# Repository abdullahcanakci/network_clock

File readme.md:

[TOC]

### What is this?

This is the second version of my clock with network time keeping with ESP12-E/F variant. On chip time keeping is good but as I experienced with DS3231 it drifts about a minute every two days. Which is not good for long time time keeping without interaction.

---

Finally I have received the board. It worked great apart from micro usb port, which was pain to solder.

---

#### Design Limits

For this project I want to have a real PCB so I won't have to fiddle with protoboards and point-to-point soldering. Also replicating a device would be so easy with a PCB.

For PCB manufacturing I shopped around my local fabs, they wanted an arm and a leg. They have a lead time of 1 month and DHL shipping which I thought they really outsource their production.

For a cheaper alternative there is JLCPCB which is cheap for board smaller than 100mm on the long side. For I couldn't really found a comparable source I have to accept their restrictions.

For display I will use 7-Segment displays with separate digits. Just because most of them are sharing their pin out I can just change them with a equivalent one easily if need arises. Biggest displays I can fit into 100 mm board is 1" character height ones which has 24-25 mm width.

---

#### Road map

Creating this device will be 4 part endeavor.

1. Hardware Selection
2. Implementation
3. Prototyping
4. Finishing

##### Hardware Selection

Can be found on Parts list.

##### Implementation

Implementation is mostly about wiring diagram and code. Both of these are done on breadboard and in minimum working order as of Jun 7, 2019. 

##### Prototyping

A prototype PCB has been sent for production in Jun 5, 2019, after receiving I will add required peripherals for interaction, better layout etc. and update the project.

By July 1, I received the boards and checked if everything was in working order. More can be found on [Prototype].

##### Finishing

Hopefully by this time everything works as expected and I wrap the project.

---

#### Parts list

|      | Name               | Description                          | Quantity |
| ---- | ------------------ | ------------------------------------ | -------- |
| 1    | ESP-12 E/F variant | uC with networking capabilities.     | 1        |
| 2    | MAX7219CWG         | Display driver with serial interface | 1        |
| 3    | AMS1117-3.3        | 3V3 voltage regulator                | 1        |
| 4    | E6-1100CUR1        | 7 Segment Display. 1" Digit height   | 4        |
| 5    | DTS-3 / STS-3      | Tactile Swich                        | 4        |
| 6    | Leds 0805(2012)    | Status leds.                         | 2        |
| 7    | 220 Ohm            | Current limit resistor for leds      | 2        |
| 8    | 10K Ohm            | Pull-up/down resistor                | 4        |
| 9    | 47K Ohm            | Max7219 current reference resistor   | 1        |
| 10   | 100nF 0805(2012)   | Decoupling capacitor                 | 2        |
| 11   | 10uF 2.5mm pitch   | Bulk capacitor for displays.         | 1        |
| 12   | 0.1"x6 header      | Serial programming header            | 1        |
| 13   |                    | Micro USB type b connector           |          |

1. ESP-12E/F for microcontroller. They are mostly same and can be interchangable.

2. MAX7219 is a serially interfaced led matrix driver. One plus of this chip is digital intensity configuration.

3. AMS1117-3.3 is a Linear voltage regulator we will use it to power our microcontroller. Display driver will use 5V direclty.

4. These displays are produced by "Strong Base Investment LTD". Datasheet can be found [here](https://img.ozdisan.com/ETicaret_Dosya/41608_1428544.pdf).  Any comparable display can be used. I left 3mm space around each display so a bit wider ones can also fit (Displays are 24mm wide, I put them inside 27mm.). As long as their pin position fits.

5. DTS-3 /STS-3 vs comparable switches can be used. Datasheet of a sample can be found [here](https://eu.mouser.com/ProductDetail/Diptronics/DTS-32N-V-B?qs=sGAEpiMZZMtFyPk3yBMYYD0iDqFNlT1wSP2u7Qqc2AE%3D).

11. 10uF bulk capacitor. Display driver is a bit power hungry. Can be substituted for no smaller than ~3uF capacitor. Board has place for 2.5mm pitch 5mm axial electrolytic capacitor. But also has place for it to lie down.
12. Regular 0.1" pitch header, pogo stick etc. can be used for programming. 
13. There are lots of Micro  USB type B connectors. I think it would be best to have a through hole one to have a better leverage against wear and tear. A comparable one can be found [here](https://eu.mouser.com/ProductDetail/Hirose-Connector/ZX62D-B-5PA830?qs=sGAEpiMZZMulM8LPOQ%252Byk6r3VmhUEyMLT8hu1C1GYL85FtczwhvFwQ%3D%3D). 

---

#### Prototype

Prototype board has been received and in working order. Final hardware design finished. Some updates  and changes from prototype board applied.

Changes made:

- Larger ground planes on both sides and more stiching.
- Thermal reliefs on all pads whether through hole or smt pad. It was hard to solder some pads on the prototype.
- Removed one of the commons connection from displays to ease routing.
- Larger board size. 42mm to 60mm. With mounting holes
- Prototype programming power source was 3V3 which wasn't enough for display driver. Changed to 5V.
- Better routing of signal traces.
- Wider trace width. 10 to 14 mil for regular, 15 to ~20mil for power traces.
- Removed Logic translator. No really need.
- Added status Leds.
- Added 4 buttons. WPS, REFRESH, OFFSET, RESET.

Schematic and the PCB gerber file can be found on the root.

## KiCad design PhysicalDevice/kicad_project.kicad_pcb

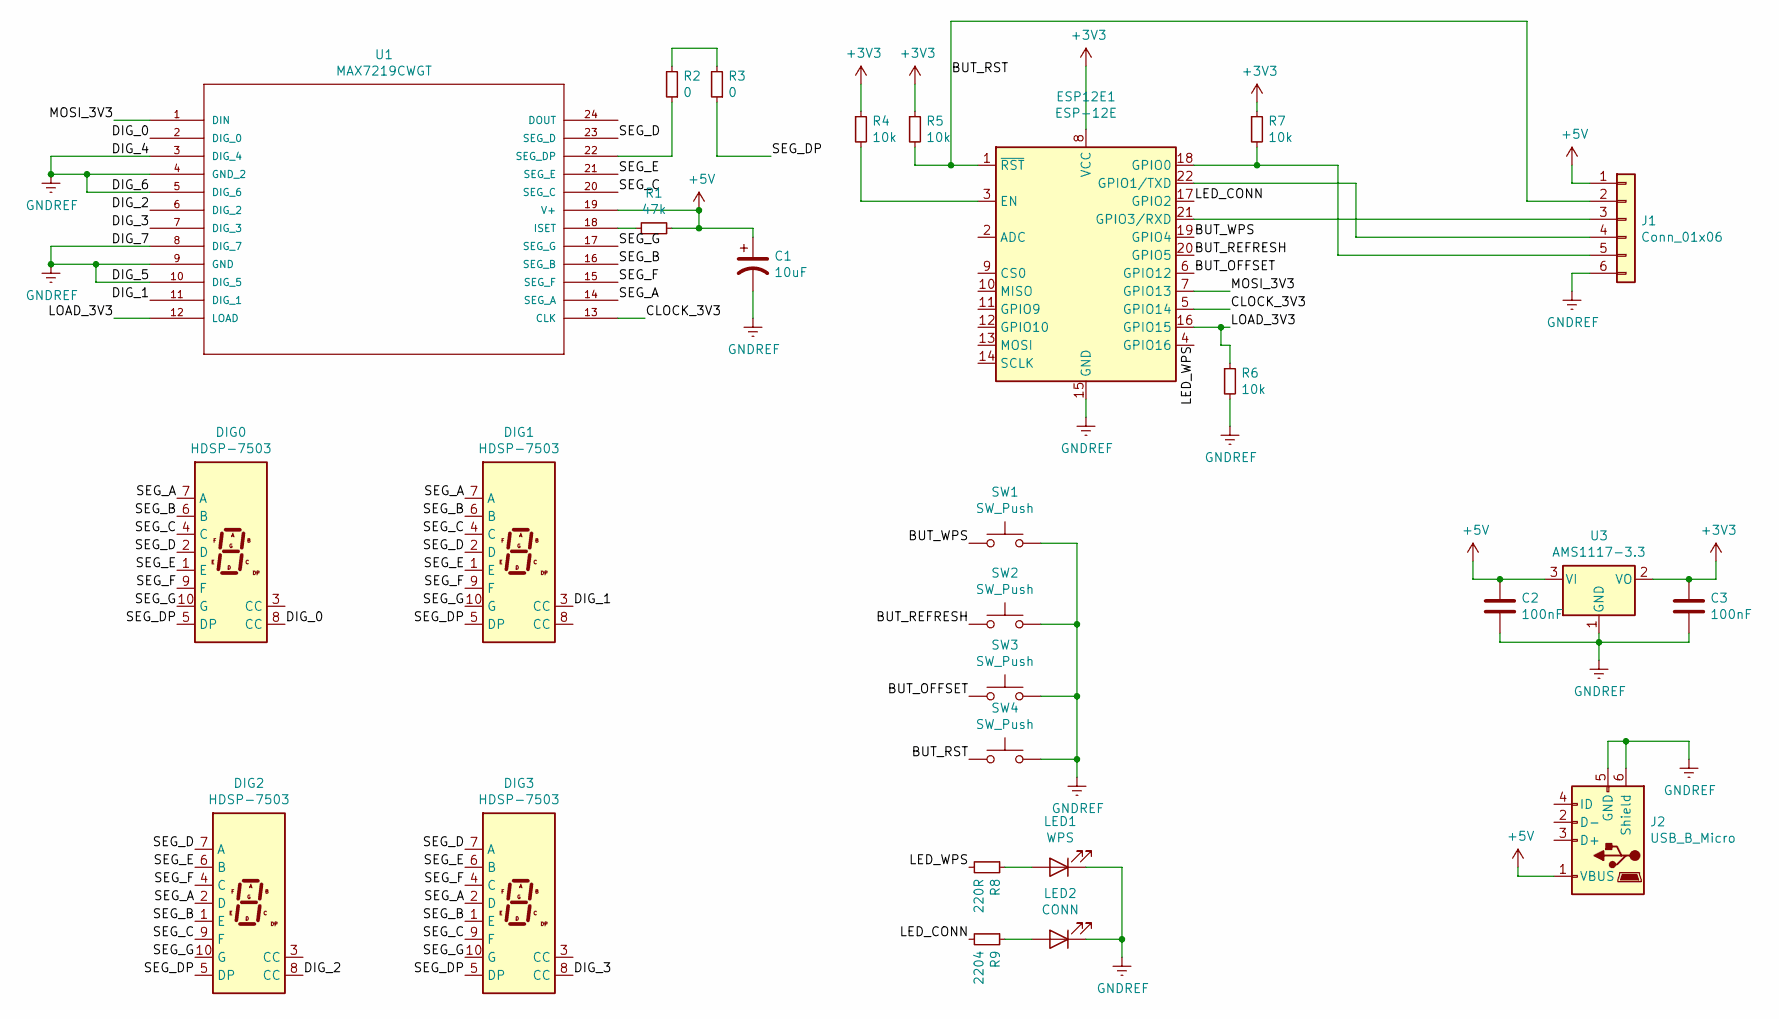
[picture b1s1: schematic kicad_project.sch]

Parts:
C1: 10uF; CP_Radial_D5.0mm_P2.50mm
C2, C3: 100nF; C_0805_2012Metric
DIG0, DIG1, DIG2, DIG3: HDSP-7503; E6-1100CUR1
ESP12E1: ESP-12E
J1: Conn_01x06; ProgrammingHeader
J2: USB_B_Micro; USB_Micro-B_Molex-105017-0001
LED1: WPS; LED_0805_2012Metric_Pad1.15x1.40mm_HandSolder
LED2: CONN; LED_0805_2012Metric_Pad1.15x1.40mm_HandSolder
R1: 47k; R_0805_2012Metric_Pad1.15x1.40mm_HandSolder
R2, R3: 0; R_0805_2012Metric_Pad1.15x1.40mm_HandSolder
R4, R5, R6, R7: 10k; R_0805_2012Metric_Pad1.15x1.40mm_HandSolder
R8: 220R; R_0805_2012Metric_Pad1.15x1.40mm_HandSolder
R9: 2204; R_0805_2012Metric_Pad1.15x1.40mm_HandSolder
SW1, SW2, SW3, SW4: SW_Push; DTS-3
U1: MAX7219CWGT; 21-0042B_24
U3: AMS1117-3.3; SOT-223-3_TabPin2

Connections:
+3V3: C3.1, ESP12E1.8 (VCC), R4.1, R5.1, R7.1, U3.2 (VO)
+5V: C1.1, C2.1, J1.1, J2.1 (VBUS), R1.2, U1.19 (V+), U3.3 (VI)
/BUT_OFFSET: ESP12E1.6 (GPIO12), SW3.1
/BUT_REFRESH: ESP12E1.20 (GPIO5), SW2.1
/BUT_RST: ESP12E1.1 (~RST), J1.2, R5.2, SW4.1
/BUT_WPS: ESP12E1.19 (GPIO4), SW1.1
/CLOCK_3V3: ESP12E1.5 (GPIO14), U1.13 (CLK)
/DIG_0: DIG0.8 (CC), U1.2 (DIG_0)
/DIG_1: DIG1.3 (CC), U1.11 (DIG_1)
/DIG_2: DIG2.8 (CC), U1.6 (DIG_2)
/DIG_3: DIG3.8 (CC), U1.7 (DIG_3)
/LED_CONN: ESP12E1.17 (GPIO2), R9.2
/LED_WPS: ESP12E1.4 (GPIO16), R8.2
/LOAD_3V3: ESP12E1.16 (GPIO15), R6.1, U1.12 (LOAD)
/MOSI_3V3: ESP12E1.7 (GPIO13), U1.1 (DIN)
/SEG_A: DIG0.7 (A), DIG1.7 (A), DIG2.2 (D), DIG3.2 (D), U1.14 (SEG_A)
/SEG_B: DIG0.6 (B), DIG1.6 (B), DIG2.1 (E), DIG3.1 (E), U1.16 (SEG_B)
/SEG_C: DIG0.4 (C), DIG1.4 (C), DIG2.9 (F), DIG3.9 (F), U1.20 (SEG_C)
/SEG_D: DIG0.2 (D), DIG1.2 (D), DIG2.7 (A), DIG3.7 (A), U1.23 (SEG_D)
/SEG_DP: DIG0.5 (DP), DIG1.5 (DP), DIG2.5 (DP), DIG3.5 (DP), R3.1
/SEG_E: DIG0.1 (E), DIG1.1 (E), DIG2.6 (B), DIG3.6 (B), U1.21 (SEG_E)
/SEG_F: DIG0.9 (F), DIG1.9 (F), DIG2.4 (C), DIG3.4 (C), U1.15 (SEG_F)
/SEG_G: DIG0.10 (G), DIG1.10 (G), DIG2.10 (G), DIG3.10 (G), U1.17 (SEG_G)
GNDREF: C1.2, C2.2, C3.2, ESP12E1.15 (GND), J1.6, J2.5 (GND), J2.6 (Shield), LED1.1 (K), LED2.1 (K), R6.2, SW1.2, SW2.2, SW3.2, SW4.2, U1.3 (DIG_4), U1.4 (GND_2), U1.5 (DIG_6), U1.8 (DIG_7), U1.9 (GND), U1.10 (DIG_5), U3.1 (GND)
unnamed: ESP12E1.3 (EN), R4.2
unnamed: ESP12E1.18 (GPIO0), J1.5, R7.2
unnamed: ESP12E1.21 (GPIO3/RXD), J1.3
unnamed: ESP12E1.22 (GPIO1/TXD), J1.4
unnamed: LED1.2 (A), R8.1
unnamed: LED2.2 (A), R9.1
unnamed: R1.1, U1.18 (ISET)
unnamed: R2.1, U1.22 (SEG_DP)
unnamed: R2.2, R3.2

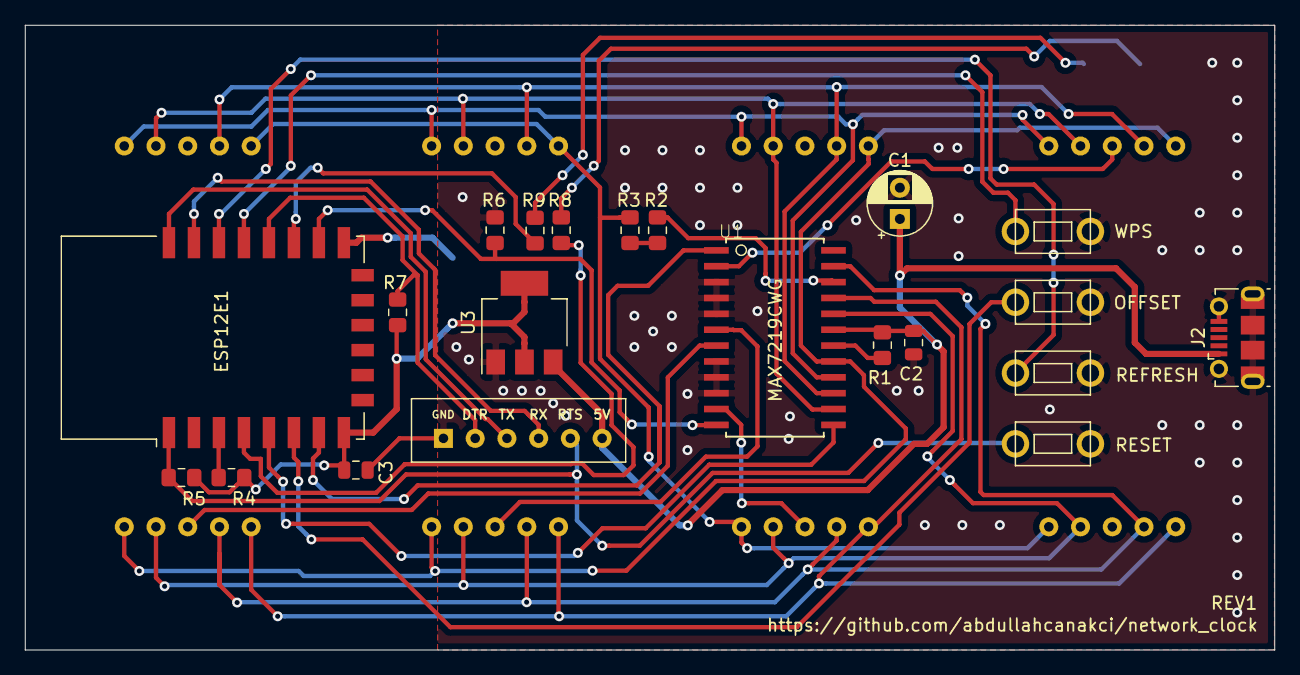
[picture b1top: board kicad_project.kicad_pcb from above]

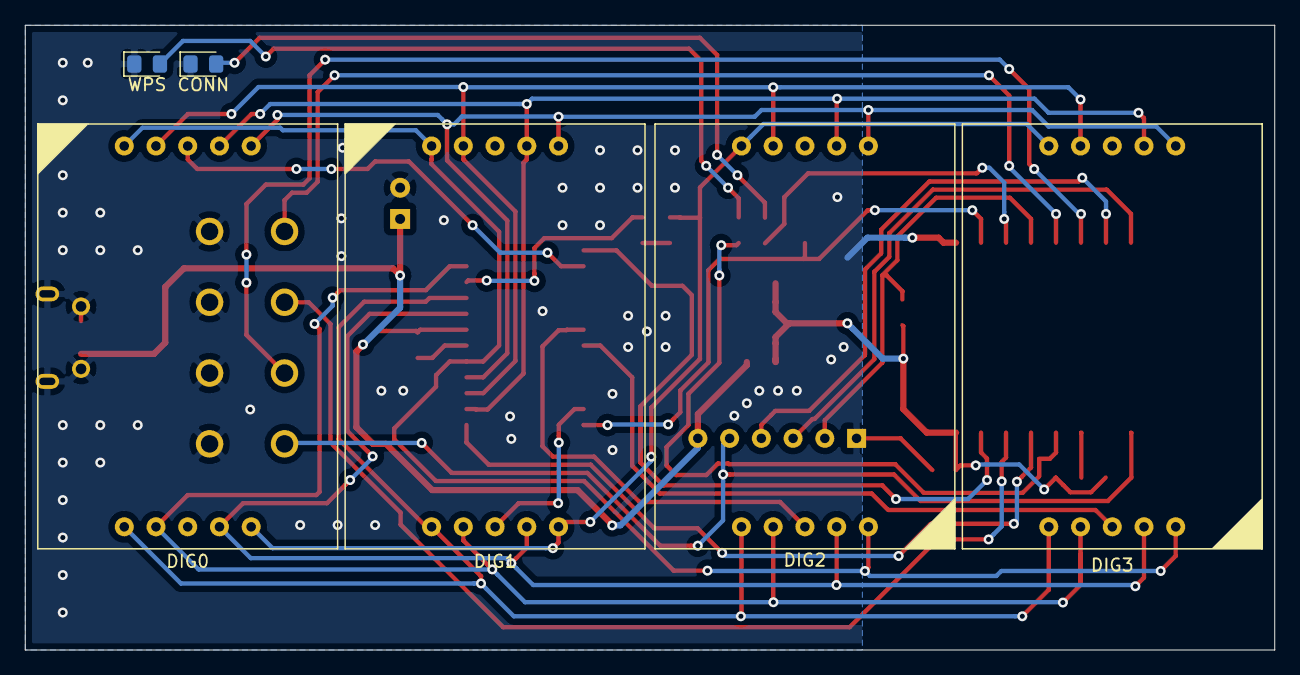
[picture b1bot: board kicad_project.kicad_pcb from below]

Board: 2 copper layers, 100.0 x 50.0 mm, 27 parts (6 on the bottom side), 33 nets.

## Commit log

2019-05-25 init
2019-05-26 Basic Serial Working. Specialization started.
    Basic serial is working. Created controllers for them and started working on them. This commit is before I gut the main.cpp
2019-05-26 Specialized controller for display
    Display is now controller by it's own class. Scanning works on first glance didn't check POV. Digit selecting works.
2019-05-26 Nodemcu problems fixed
    Nodemcu created problems when I want to use pins to drive mosfet gates. I fixed it with second 595 to create extra 8 bits of control to control mosfets. Persistence of vision works.
2019-05-26 fix delay
2019-05-27 Interrupt based updates. Time servers and parsing local timekeeping.
    Updates that need to be time sensitive moved to the Ticker from esp8266/arduinocore it works as expected.
    Display, UDP package checking clock dot etc are implemented.
    NTP time server connection implemented. for local timekeeping and parsing RTCLib from Adafruit used. I have used it before, familiar with it. May change with something smaller later.
    Time to display parsing imlemented, works.
2019-05-27 Dot is working.
2019-06-04 Move to MAX7219
    Okay, at first I was gonna use 595 as drivers and use 1" 7 segment led displays. The problem is there is not much displays with 1 chip per segment. With 595 I was gonna use sole 3V3 logic everywhere.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
2019-06-04 Code cleanup
2019-06-04 Fixed dot working.
    Relocated some code
2019-06-05 Updated readme. Schematic and PCB added
2019-06-07 updated and rewrote readme.md
2019-06-15 RTClib name mismatch fixed. Interrupts are moved into flag based events within loop()
2019-06-21 implemented rudimentary interrupt debouncing
2019-06-21 HW interrupt based Debounce removed.
2019-06-21 implemented refresh button and respective action
2019-06-24 WPS is implemented. EEPROM implemented.
2019-06-24 init physical device
2019-06-25 created schematic and routed pcb
2019-06-25 Board fully routed. Gerber file generated.
2019-06-26 added an extra button, 2 leds.
2019-06-26 added leds and rerouted some bits to be more tidy
2019-07-01 pre track witdh change
2019-07-01 changed min routing size from 0.25mm(~9.8mil) to 0.35(~13.4mil)
2019-07-02 removed kicad files. To much Clutter. Will update Gerber accordinly
2019-07-02 Added Gerber
2019-07-02 Removed Kicad Folder
2019-07-04 Added schematic and updated readme
2019-07-07 Basic server created. Basic webpage created. no interaction.
2019-07-08 Json answering works. Webpage mostly works
2019-07-08 Full exchange between server and client established
2019-07-09 Persistence of credentials are implemented. Portal device interaction implemented.
2019-07-09 Fixed an issue where writing to a file created an EOM marker, before EOL one. Changed to CSV. reorganized some files.
2019-07-09 JSON post request is simplified
2019-07-09 Basic auth implemented.
2019-07-09 Code refactoring.
2019-07-10 Updated PCB with mounting holes. Larger PCB.
2019-07-11 Fixed frontend.
    Fixed frontend. Changed some CSS rules to be more stylish. Portrait mode works good enough. Mobile keyboard breaks layout.
2019-07-12 Small forgotten things
2019-07-12 Removed 'Ticker'\n\n Removed library ticker. Implemented own solution. Interrupts didn't worked as well as I hoped with wifi stack
2019-07-15 Moved Interruption init out of setup
2019-07-15 Implemented boot modes.
    Implemented different boot modes based on button inputs.
    Fixed edge cases on time based functions routine.
    Time left untouched. Time offset done on buffer parsing.
    Credentials file restore implemented.
    WPS connection edge case errors fixed.
    WPS conn. info on screen
2019-08-03 Added device pictures and updated readme
2019-08-03 removed comments from gthumb(?)
